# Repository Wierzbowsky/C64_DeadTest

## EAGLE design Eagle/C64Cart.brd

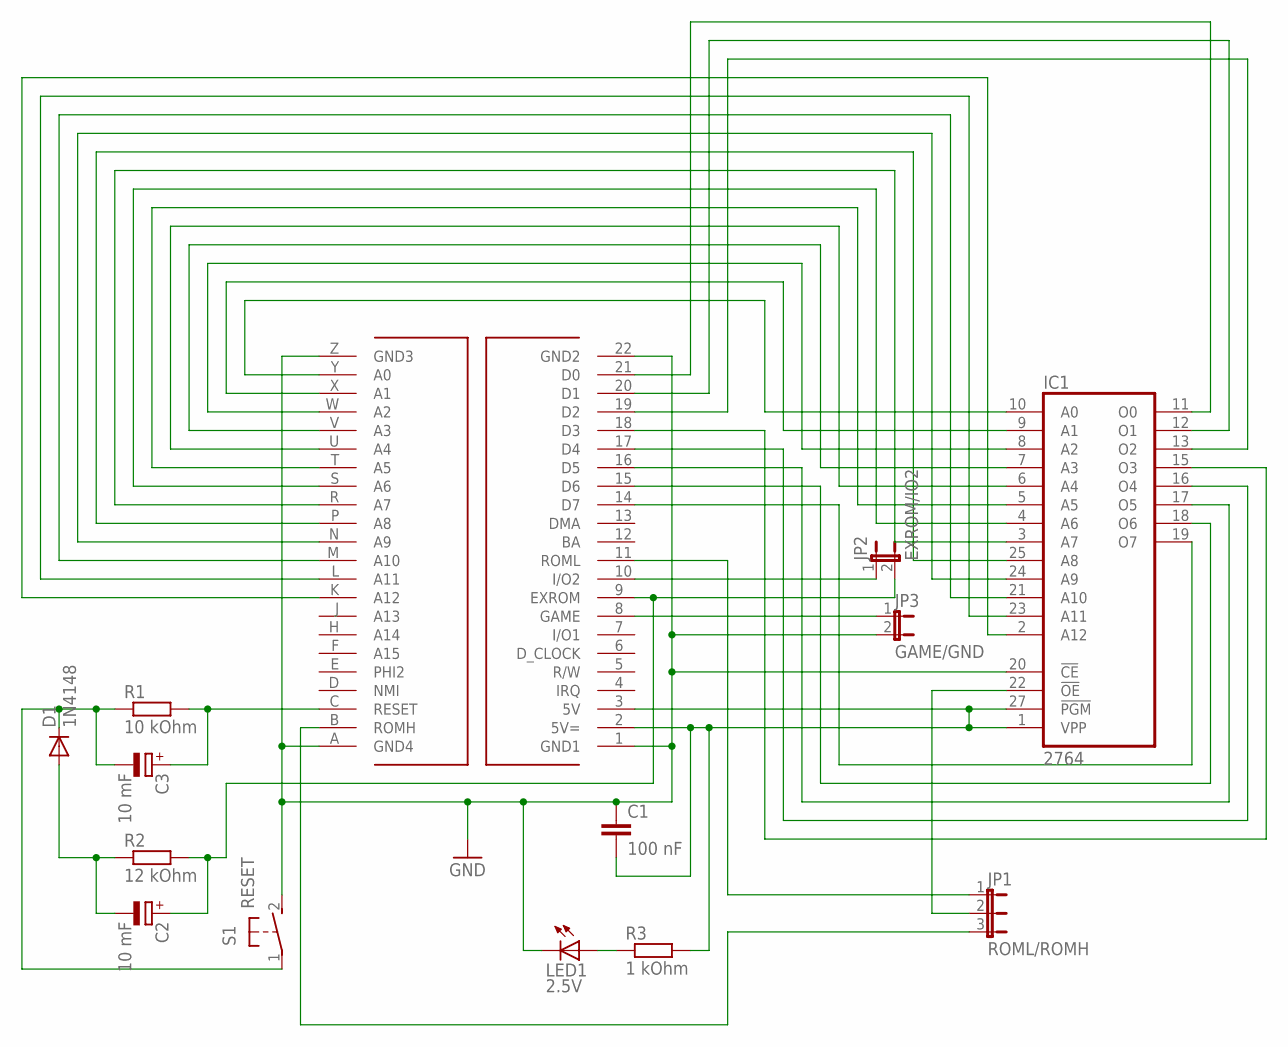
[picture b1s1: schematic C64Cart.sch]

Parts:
C1: 100 nF; C050-025X075
C2, C3: 10 mF; E2-5
D1: 1N4148; DO35-7
IC1: 2764; DIL28
JP1: ROML/ROMH; JP2
JP2: EXROM/IO2; JP1
JP3: GAME/GND; JP1
LED1: 2.5V; LED3MM
R1: 10 kOhm; 0204/7
R2: 12 kOhm; 0204/7
R3: 1 kOhm; 0204/7
S1: RESET; B3F-31XX
U$1: C64_CN; CARTRIDGE

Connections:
C64CART: IC1.10 (A0), U$1.Y (A0)
GND: C1.1, IC1.14 (GND), IC1.20 (!CE), JP3.2, LED1.K (C), S1.2 (S), U$1.1 (GND1), U$1.22 (GND2), U$1.A (GND4), U$1.Z (GND3)
unnamed: JP3.1, U$1.8 (GAME)
unnamed: IC1.22 (!OE), JP1.2
unnamed: IC1.18 (O6), U$1.15 (D6)
unnamed: IC1.9 (A1), U$1.X (A1)
unnamed: IC1.8 (A2), U$1.W (A2)
unnamed: IC1.7 (A3), U$1.V (A3)
unnamed: IC1.6 (A4), U$1.U (A4)
unnamed: IC1.5 (A5), U$1.T (A5)
unnamed: IC1.4 (A6), U$1.S (A6)
unnamed: IC1.3 (A7), U$1.R (A7)
unnamed: IC1.25 (A8), U$1.P (A8)
unnamed: IC1.24 (A9), U$1.N (A9)
unnamed: IC1.21 (A10), U$1.M (A10)
unnamed: IC1.23 (A11), U$1.L (A11)
unnamed: IC1.2 (A12), U$1.K (A12)
unnamed: IC1.11 (O0), U$1.21 (D0)
unnamed: IC1.13 (O2), U$1.19 (D2)
unnamed: IC1.17 (O5), U$1.16 (D5)
unnamed: IC1.19 (O7), U$1.14 (D7)
unnamed: IC1.15 (O3), U$1.18 (D3)
unnamed: IC1.16 (O4), U$1.17 (D4)
unnamed: C3.-, D1.C, R1.1, S1.1
unnamed: C2.+, JP2.2, R2.2, U$1.9 (EXROM)
unnamed: C3.+, R1.2, U$1.C (RESET)
unnamed: IC1.12 (O1), U$1.20 (D1)
unnamed: C2.-, D1.A, R2.1
unnamed: LED1.A, R3.1
unnamed: JP2.1, U$1.10 (I/O2)
unnamed: JP1.1, U$1.11 (ROML)
unnamed: JP1.3, U$1.B (ROMH)
VCC: C1.2, IC1.1 (VPP), IC1.27 (!PGM), IC1.28 (VCC), R3.2, U$1.2 (5V=), U$1.3 (5V)

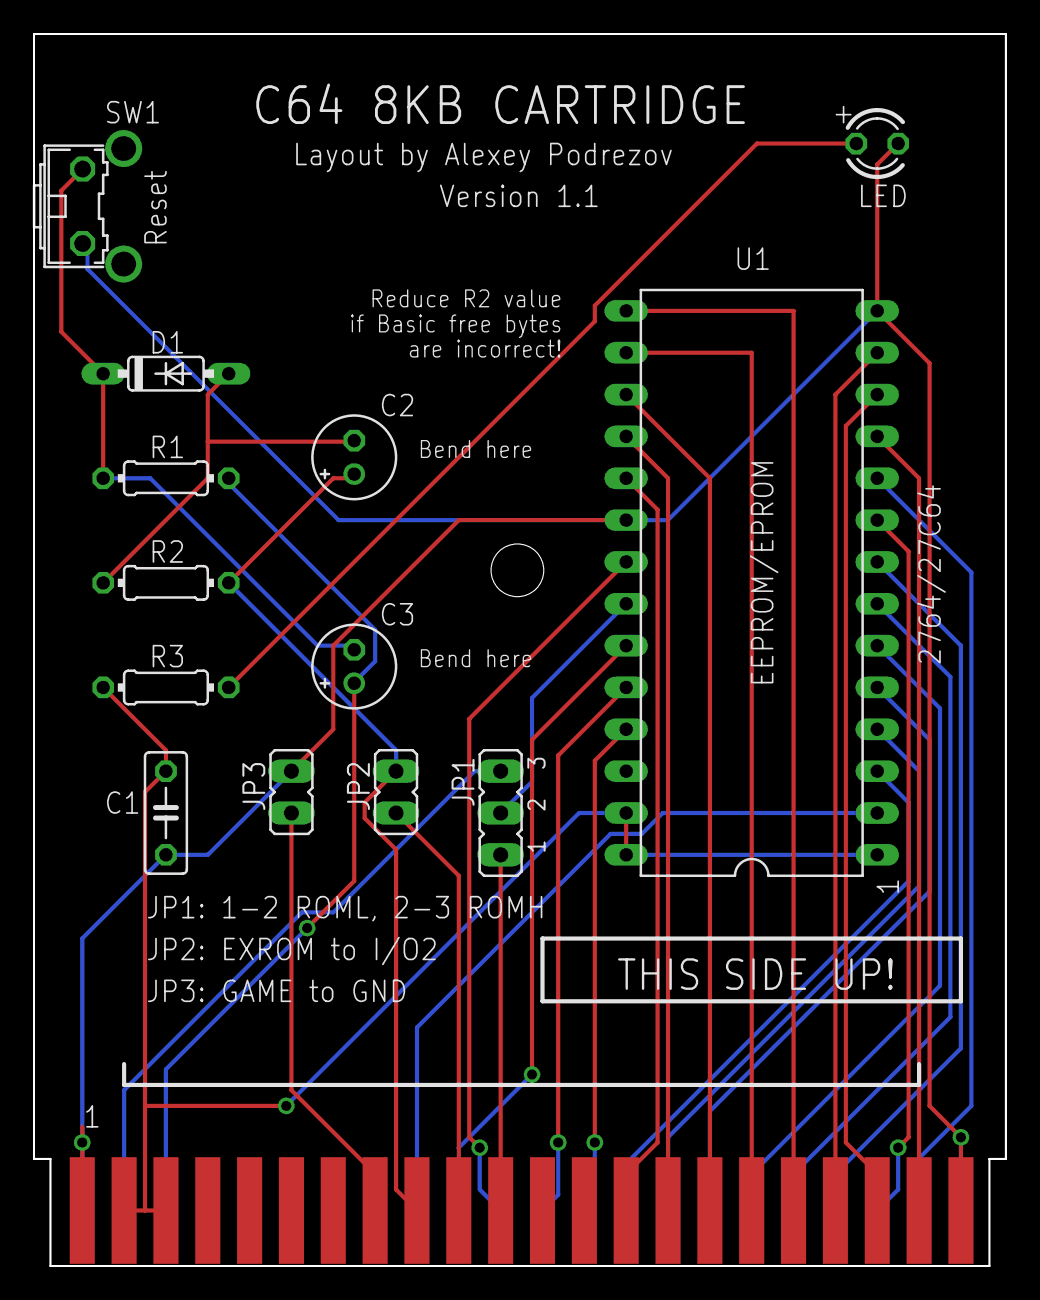
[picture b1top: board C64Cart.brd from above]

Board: 2 copper layers, 59.0 x 74.8 mm, 14 parts (0 on the bottom side), 33 nets.

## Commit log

2015-12-30 :boom::camel: Added .gitattributes & .gitignore files
2015-12-30 Fixed 8kb cartridge prototype
    Fixed 8kb cartridge prototype, the first prototype had a missing
    connection and wrong labeling
2015-12-30 ROM for DeadTest (not made by RBSC)
    ROM for DeadTest (not made by RBSC)
2016-05-27 Partslist
2017-05-20 Updated board folder
